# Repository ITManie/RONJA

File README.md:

# 

Project to contest MCU letí 2015.

## Part list
 - 2x [PICAxe 08M2](http://www.gme.cz/mikrokontroler-picaxe-08m2-p772-029)
 - 2x [Fairchild QRD1114](http://www.gme.cz/qrd1114-p523-265)
 - 2x [100R resistor](http://www.gme.cz/rm-100r-0204-0-4w-1-hitano-p119-398)
 - 4x [10k resistor](http://www.gme.cz/rm-10k-0204-0-4w-1-hitano-p119-396)
 - 2x [22k resistor](http://www.gme.cz/rm-22k-0204-0-4w-1-hitano-p119-407)
 - 2x [RS232 connector](http://www.gme.cz/konektor-can-9-z-p801-040)
 - 5V power supply (for example USB)

## Schema

## Documentation
Documentation in Czech you can found in [docs](https://github.com/ITManie/RONJA/tree/master/docs) directory.

## License
RONJA is licensed under the GPL FDL v1.3 license:

 > Copyright (c)  2015  Adam Rozbořil and Roman Ondráček.
 >
 > Permission is granted to copy, distribute and/or modify this document
 > under the terms of the GNU Free Documentation License, Version 1.3
 > or any later version published by the Free Software Foundation;
 > with no Invariant Sections, no Front-Cover Texts, and no Back-Cover Texts.
 > A copy of the license is included in the section entitled "GNU
 > Free Documentation License".

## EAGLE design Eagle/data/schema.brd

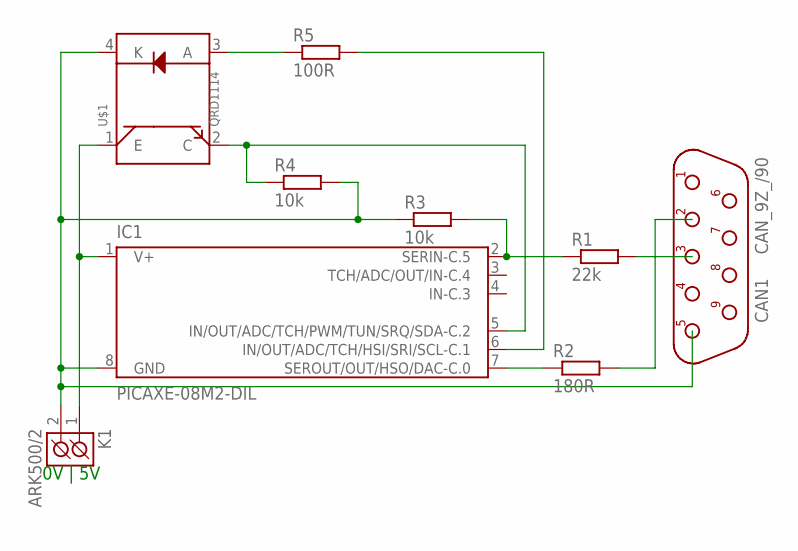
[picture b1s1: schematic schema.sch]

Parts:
CAN1: CAN_9Z_/90; CAN9Z/90
IC1: PICAXE-08M2-DIL; DIL8
K1: ARK500/2
R1: 22k; 0207/10
R2: 180R; 0207/10
R3, R4: 10k; 0207/10
R5: 100R; 0207/10
U$1: QRD1114

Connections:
unnamed: IC1.7 (SEROUT/OUT/HSO/DAC-C.0), R2.1
unnamed: CAN1.3, R1.2
unnamed: CAN1.2, R2.2
unnamed: R5.1, U$1.3 (A)
unnamed: IC1.6 (IN/OUT/ADC/TCH/HSI/SRI/SCL-C.1), R5.2
unnamed: IC1.5 (IN/OUT/ADC/TCH/PWM/TUN/SRQ/SDA-C.2), R4.1, U$1.2 (C)
unnamed: CAN1.5, IC1.8 (GND), K1.2 (K2), R3.1, R4.2, U$1.4 (K)
unnamed: IC1.1 (V+), K1.1 (K1), U$1.1 (E)
unnamed: IC1.2 (SERIN-C.5), R1.1, R3.2

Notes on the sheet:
0V | 5V

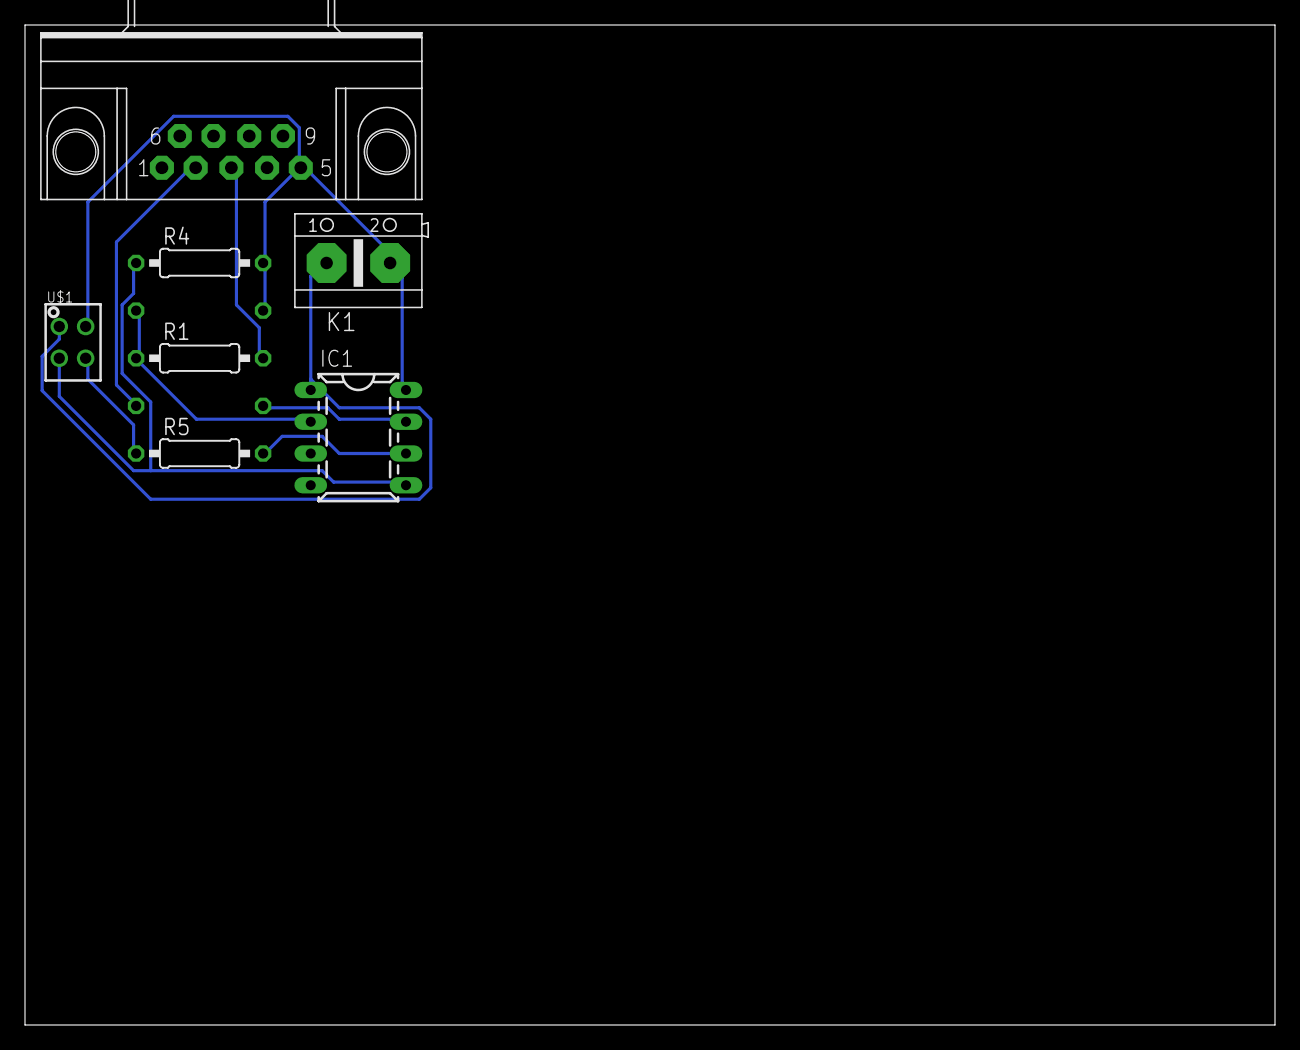
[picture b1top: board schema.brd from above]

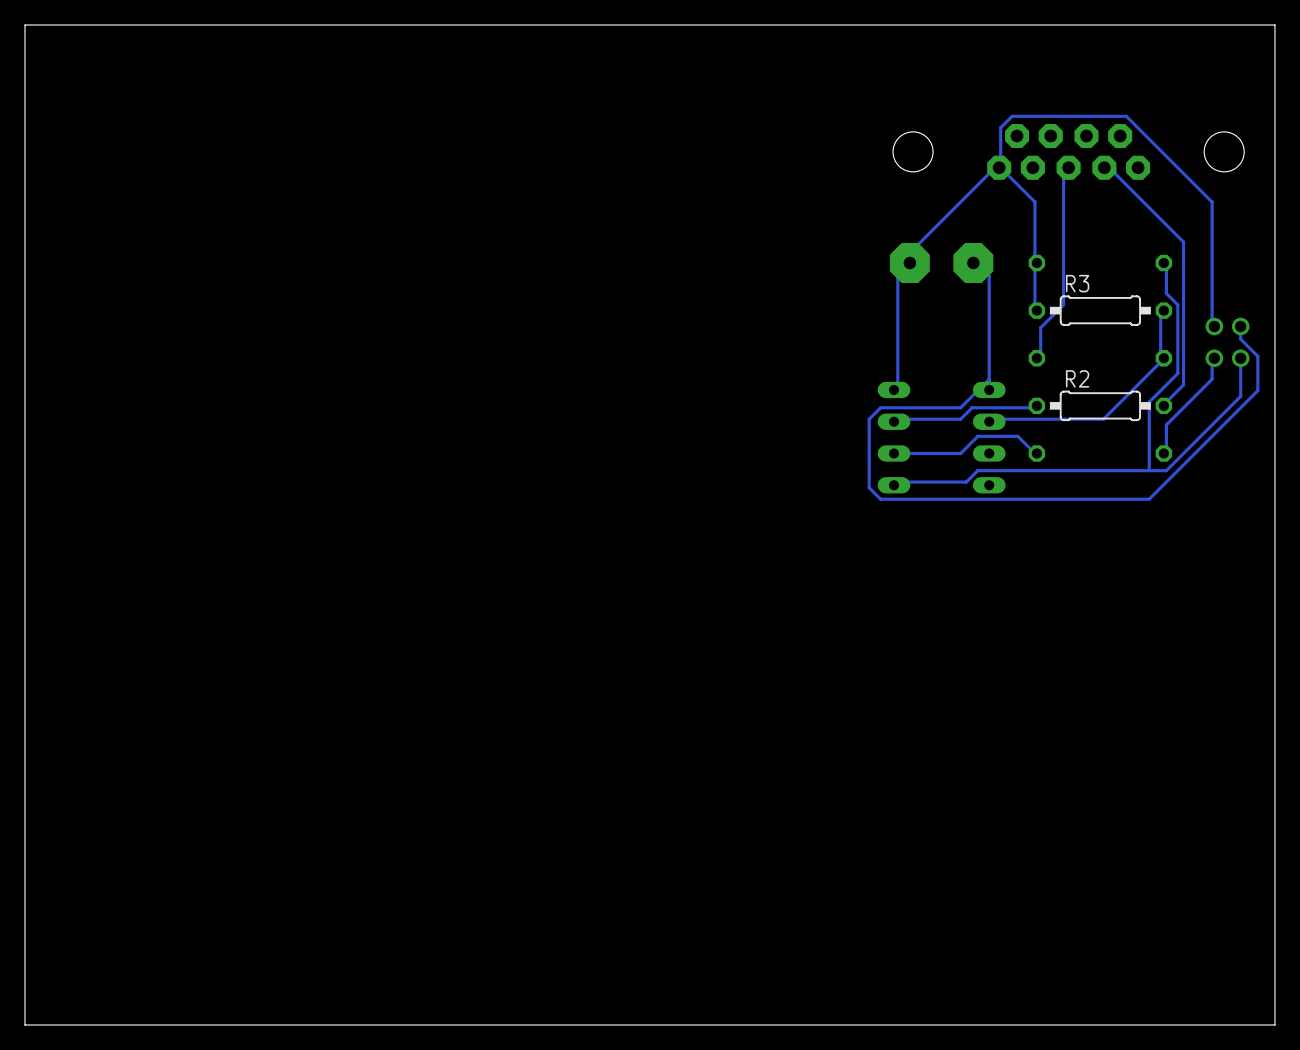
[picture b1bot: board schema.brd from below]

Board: 2 copper layers, 100.0 x 80.0 mm, 9 parts (2 on the bottom side), 9 nets.

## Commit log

2015-04-09 Vytvořen README
2015-06-02 Beta verze programu pro PICAxe
2015-06-08 Převod písmen na čísla v dvojkové soustavě
2015-06-09 Úprava zdrojového kódu
2015-06-09 Přidán ovladač pro RONJU
2015-06-09 Pár menších změn
2015-06-09 Přidány další znaky a přidán Easter egg
2015-06-09 Úprava adresářové struktury
2015-06-09 Přidání nových znaků do driveru a oprava převodu znaků v MCU
2015-06-10 Oprava kódu
2015-06-10 Změny v driveru
2015-06-10 Schéma + knihovny pro Eagle
2015-06-10 Úprava programu pro MCU
2015-06-10 Přidáno dekódování znaků z RONJi
2015-06-10 Verze 1.0.0, měla by být OK
2015-06-10 Úprava schématu
2015-06-10 Oprava chyby v přijímacím SW pro MCU
2015-06-10 Přidání licence
2015-06-10 Úprava odesílacího SW pro MCU
2015-06-10 Změna verze licence GNU FDL z plain-text na markdown
2015-06-10 Úprava souborů pro SW Eagle
2015-06-10 Odstraněn easter egg
2015-06-11 Doladění driveru
2015-06-11 Úprava odesílajícího SW pro MCU
2015-06-11 Optimalizace "špageti kódu"
2015-06-11 Pokus o opravu odesílacího SW pro MCU
2015-06-11 Částečná oprava odesílacího SW pro MCU
2015-06-11 Testovací SW pro odesílání dat
2015-06-11 Změněn způsob posílání znaků
2015-06-11 Přidány ASCII kódy 10 a 13 v odesílači pro MCU
2015-06-11 Přidáno schéma zapojení
2015-06-11 Úprava driveru - odesílání písmen
2015-06-11 Prasácké řešení problému s novým řádkem a dekódováním.
2015-06-11 Oprava chyby
2015-06-11 Přidána dokumentace
2015-06-11 Oprava SW pro MCU
2015-06-11 Updatovaná binárka driveru
2015-06-12 Úprava dokumentace
2015-06-12 Úprava popisu driveru ve Windows
2015-06-12 Snad konečná úprava odesílacího SW pro MCU PICAxe
2015-06-12 Snad onečná úprava přijímacího SW pro MCU PICAxe
2015-06-12 Formát kódu driveru
2015-09-24 Add Travis CI for RONJADriver
2015-09-24 Přidán krátký popisek
2015-09-24 Přidán obrázek stavu Travis CI
2016-03-08 [LICENSE] Added plain-text license
2016-03-08 [README] Added badges
2016-04-24 [LICENSE] Repair name of markdown version of license
2016-04-24 [Eagle] Remove library
2016-04-24 [Picaxe] Renamed files
2016-04-24 [RONJADriver] Refactored Decode function, repaired improper exceptions and changed the structure of the project
2016-04-24 [RONJADriver] Added license header
2016-04-24 [RONJADriver] Update icon location
2016-04-24 [PICAXE] Added license header
2016-04-24 [README] Added logo, schema, docs and license
2016-04-24 [docs] Renamed files
2016-04-24 [Eagle] Removed surplus layers, packages and symbols
2016-04-24 [README] Fixed typos
2016-04-24 [Eagle] Minified schema

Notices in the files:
parts and their libraries:
Copyright (C) PaJa 2011-2014
